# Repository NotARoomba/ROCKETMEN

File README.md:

<h1 align="center">
  <br>
  
  <br>
  ROCKETMEN
  <br>
</h1>

<h4 align="center">Project files for a custom model rocket and embedded flight controller.</h4>

<div align="center">

</div>

<p align="center">
  <a href="#key-features">Key Features</a> •
  <a href="#how-to-use">How To Use</a> •
  <a href="#credits">Credits</a> •
  <a href="#license">License</a>
</p>

## Key Features

- Small (12cm x 5cm) microcontroller with
  - STM32 MCU
  - USB-C with USB-Serial CH340 chip
  - LoRa communication at 433 Mhz from the LLCC68 chip
  - IMU that proides gyro/accelerometer data
  - Pressure and temperature sensors
- Website that provides data in real time (websockets)
- Client that sends data from the ground station to the website

## How To Use

To clone and run this application, you'll need [Git](https://git-scm.com) and [Rust](https://www.rust-lang.org/) installed on your computer. From your command line:

```bash
# Clone this repository
$ git clone https://github.com/NotARoomba/ROCKETMEN

# Go into the repository
$ cd ROCKETMEN

# Go into the server
$ cd Talos/Server

# Run the app
$ cargo run
```

## Credits

This software uses the following open source packages:

- [Rust](https://www.rust-lang.org/)
- [Node.js](https://nodejs.org/)

## You may also like...

- [Niveles De Niveles](https://github.com/NotARoomba/NivelesDeNiveles) - A real-time flood alert app
- [SupDoc](https://github.com/NotARoomba/SupDoc) - An app facilitating doctor/patient communication

## License

MIT

---

> [notaroomba.dev](https://notaroomba.dev) &nbsp;&middot;&nbsp;
> GitHub [@NotARoomba](https://github.com/NotARoomba) &nbsp;&middot;&nbsp;

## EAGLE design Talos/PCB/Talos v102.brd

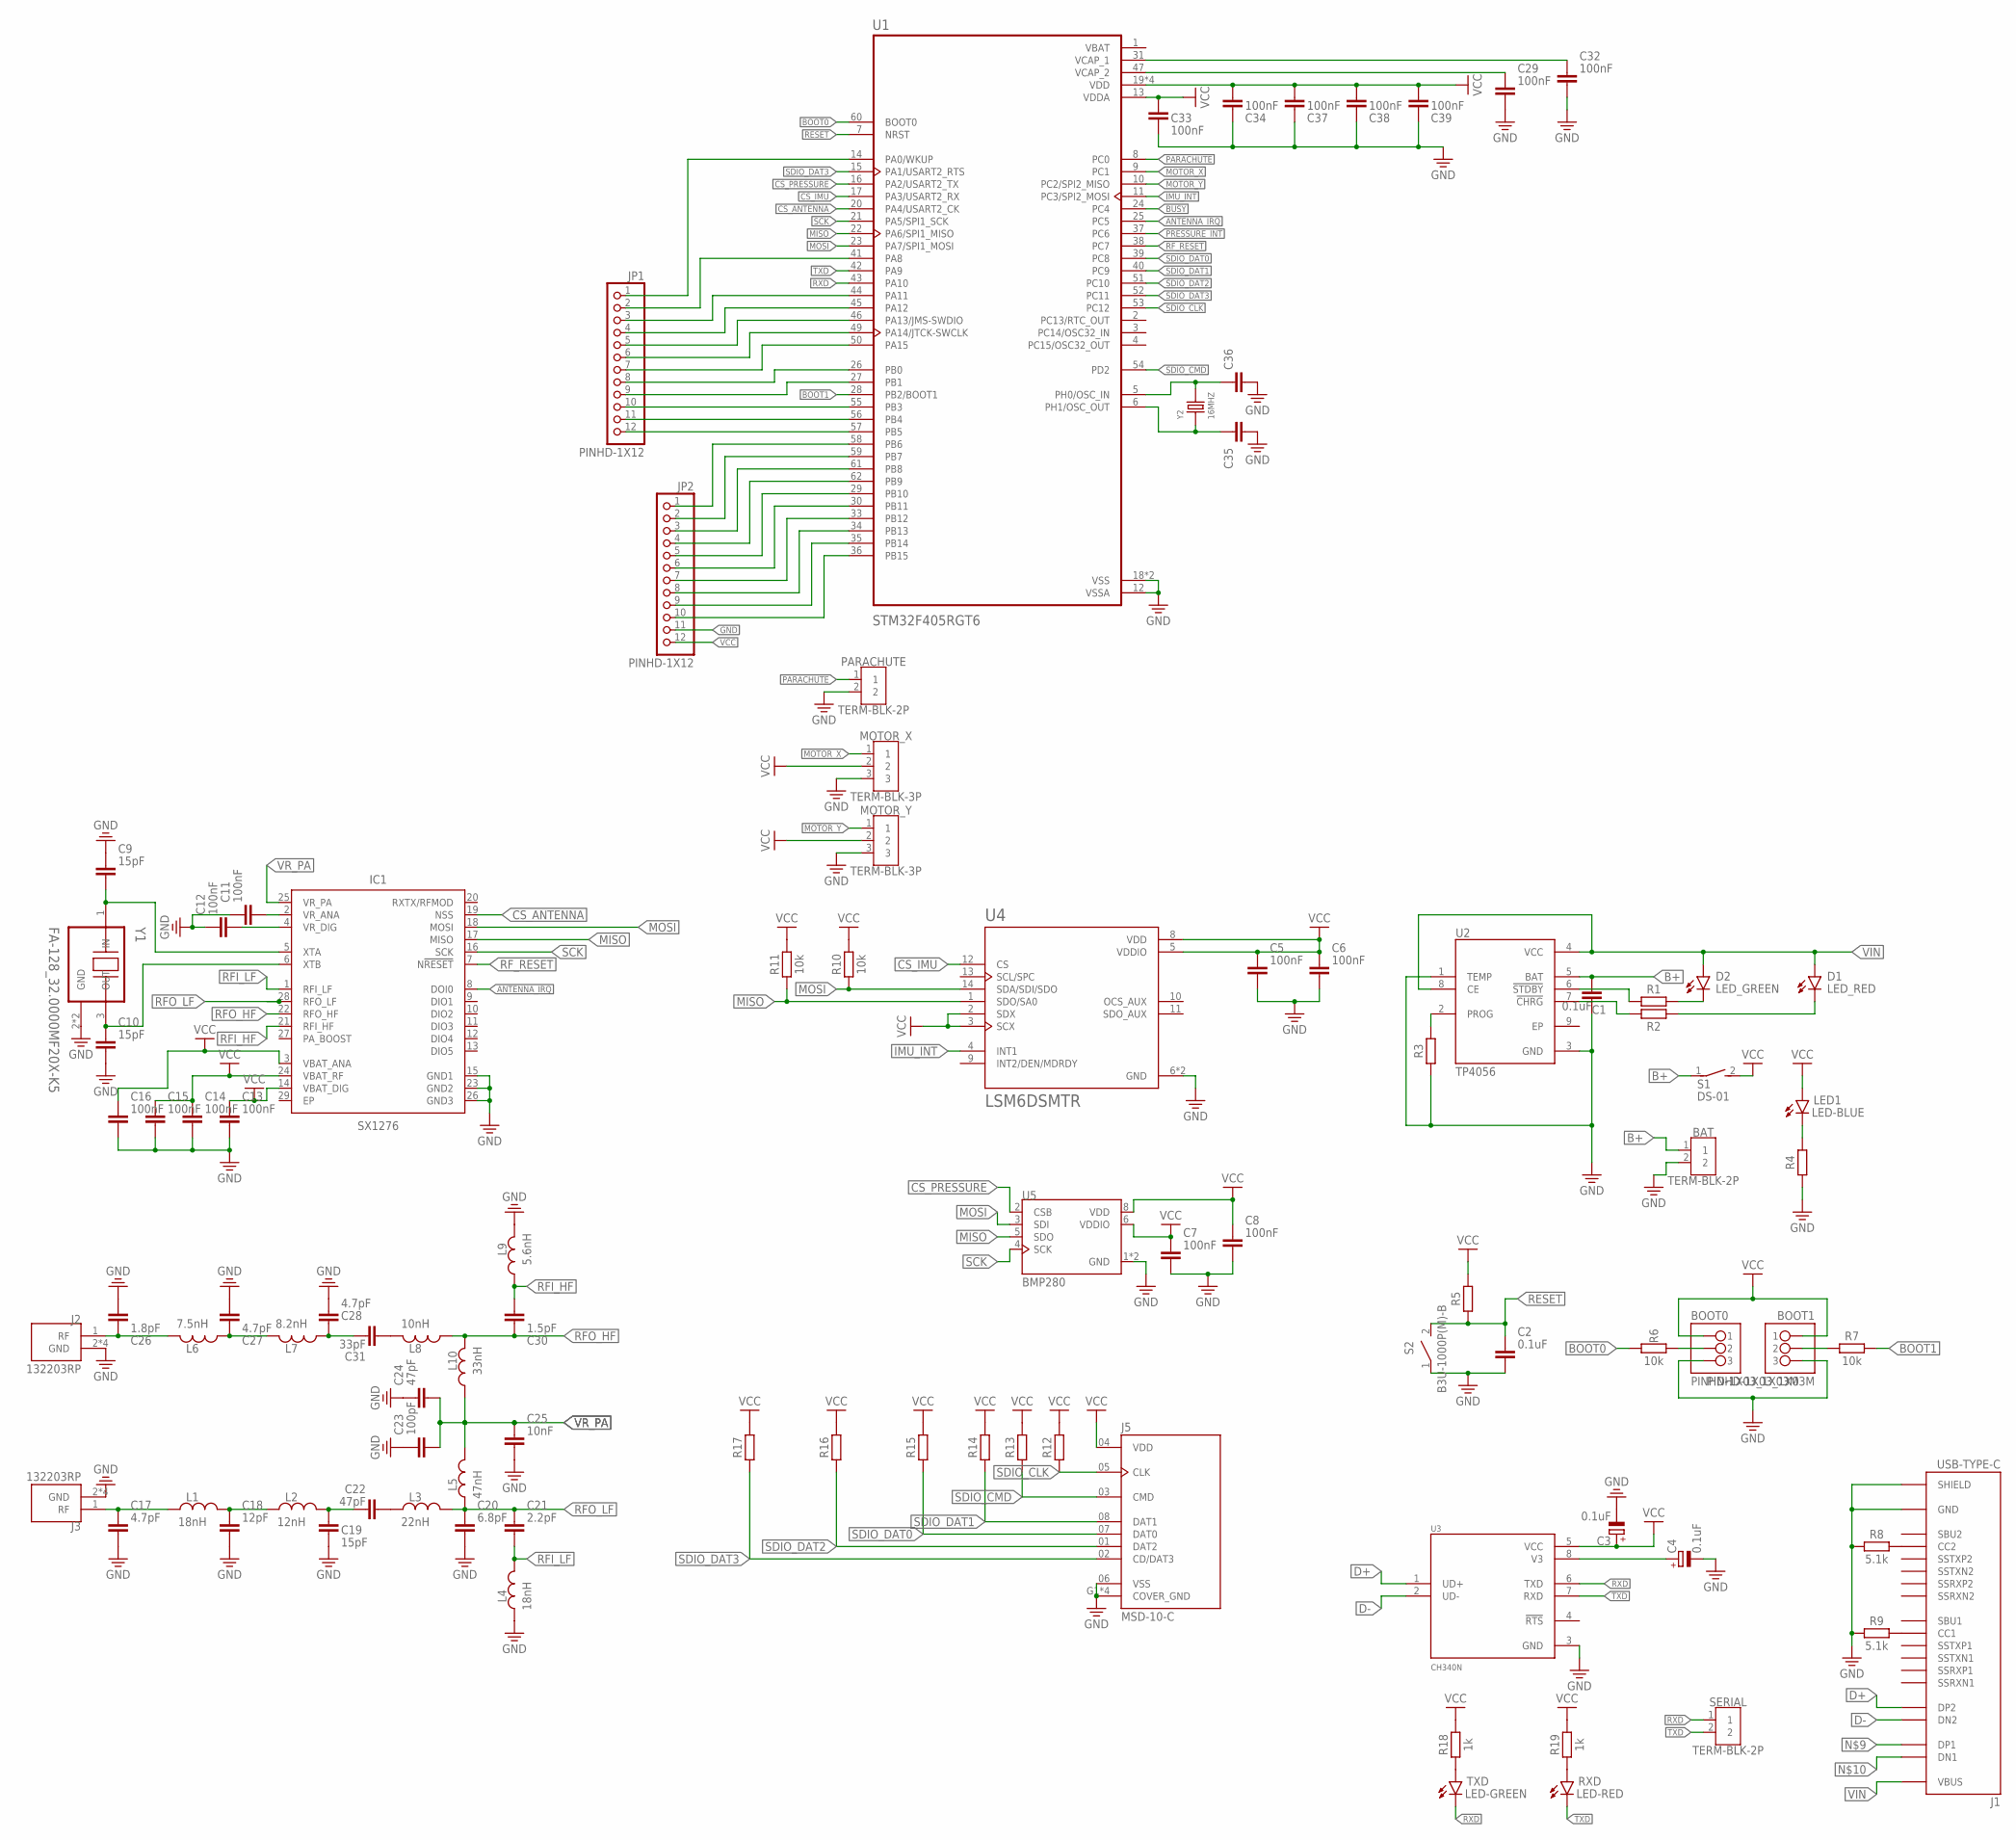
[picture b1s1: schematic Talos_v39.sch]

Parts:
BAT: TERM-BLK-2P; TERMBLK_254-2N
BOOT0, BOOT1: PINHD-1X03_1X03M; 1X03
C1, C2: 0.1uF; CAPC1005X60
C3, C4: 0.1uF; CAPMP3216X180N
C5, C6, C7, C8, C11, C12, C13, C14, C15, C16, C29, C32, C33, C34, C37, C38, C39: 100nF; CAPC1005X60
C9, C10, C19: 15pF; CAPC1005X60
C17, C27, C28: 4.7pF; CAPC1005X60
C18: 12pF; CAPC1005X60
C20: 6.8pF; CAPC1005X60
C21: 2.2pF; CAPC1005X60
C22, C24: 47pF; CAPC1005X60
C23: 100pF; CAPC1005X60
C25: 10nF; CAPC1005X60
C26: 1.8pF; CAPC1005X60
C30: 1.5pF; CAPC1005X60
C31: 33pF; CAPC1005X60
C35, C36: C_CHIP-0402(1005-METRIC); CAPC1005X60
D1: LED_RED; LEDC1608X35N_FLAT-R
D2: LED_GREEN; LEDC1608X35N_FLAT-G
IC1: SX1276; QFN65P600X600X100-29T480
J1: USB-TYPE-C; CUI_UJ31-CH-31-SMT-TR
J2, J3: 132203RP
J5: MSD-10-C; CUI_MSD-10-C
JP1, JP2: PINHD-1X12; 1X12
L1, L4: 18nH; INDC1006X60N
L2: 12nH; INDC1006X60N
L3: 22nH; INDC1006X60N
L5: 47nH; INDC1006X60N
L6: 7.5nH; INDC1006X60N
L7: 8.2nH; INDC1006X60N
L8: 10nH; INDC1006X60N
L9: 5.6nH; INDC1006X60N
L10: 33nH; INDC1006X60N
LED1: LED-BLUE; LEDC1608X39N_B
MOTOR_X: TERM-BLK-3P; TERMBLK_254-3N
MOTOR_Y: TERM-BLK-3P; TERMBLK_254-3N
PARACHUTE: TERM-BLK-2P; TERMBLK_254-2N
R1, R2, R4, R5, R12, R13, R14, R15, R16, R17: R_CHIP-0402(1005-METRIC); RESC1005X40
R3: RESISTOR__CHIP-0402(1005-METRIC); RESC1005X40
R6, R7, R10, R11: 10k; RESC1005X40
R8, R9: 5.1k; RESC1005X40
R18, R19: 1k; RESC1005X40
RXD: LED-RED; LEDC1608X39N_R
S1: DS-01
S2: B3U-1000P(M)-B
SERIAL: TERM-BLK-2P; TERMBLK_254-2N
TXD: LED-GREEN; LEDC1608X39N_G
U1: STM32F405RGT6; QFP50P1200X1200X160-64N
U2: TP4056; SOP127P600X175-9N
U3: CH340N; SOIC127P600X160-8N
U4: LSM6DSMTR; PQFN50P300X250X86-14N
U5: BMP280; XDCR_BMP280
Y1: FA-128_32.0000MF20X-K5; OSCCC200X160X50
Y2: 16MHZ; HC49US

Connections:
ANTENNA_IRQ: IC1.8 (DOI0), U1.25 (PC5)
B+: BAT.1, C1.2, S1.1, U2.5 (BAT)
BOOT0: R6.1, U1.60 (BOOT0)
BOOT1: R7.2, U1.28 (PB2/BOOT1)
BUSY: U1.24 (PC4)
CS_ANTENNA: IC1.19 (NSS), U1.20 (PA4/USART2_CK)
CS_IMU: U1.17 (PA3/USART2_RX), U4.12 (CS)
CS_PRESSURE: U1.16 (PA2/USART2_TX), U5.2 (CSB)
D+: J1.B6 (DP2), U3.1 (UD+)
D-: J1.B7 (DN2), U3.2 (UD-)
GND: BAT.2, BOOT0.3, BOOT1.3, C1.1, C2.2, C3.2 (-), C4.2 (-), C5.2, C6.2, C7.2, C8.2, C9.1, C10.2, C11.1, C12.1, C13.2, C14.2, C15.2, C16.2, C17.2, C18.2, C19.2, C20.2, C23.1, C24.1, C25.2, C26.2, C27.2, C28.2, C29.2, C32.2, C33.2, C34.2, C35.2, C36.2, C37.2, C38.2, C39.2, IC1.15 (GND1), IC1.23 (GND2), IC1.26 (GND3), J1.1 (SHIELD), J1.2 (SHIELD), J1.3 (SHIELD), J1.4 (SHIELD), J1.5 (SHIELD), J1.6 (SHIELD), J1.A1 (GND), J1.A12 (GND), J1.B1 (GND), J1.B12 (GND), J1.S1 (SHIELD), J1.S2 (SHIELD), J2.2 (GND), J2.3 (GND), J2.4 (GND), J2.5 (GND), J3.2 (GND), J3.3 (GND), J3.4 (GND), J3.5 (GND), J5.06 (VSS), J5.G1 (COVER_GND), J5.G2 (COVER_GND), J5.G3 (COVER_GND), J5.G4 (COVER_GND), JP2.11, L4.1, L9.1, MOTOR_X.3, MOTOR_Y.3, PARACHUTE.2, R3.1, R4.1, R8.1, R9.1, S2.1, U1.12 (VSSA), U1.18 (VSS), U1.63 (VSS), U2.1 (TEMP), U2.3 (GND), U3.3 (GND), U4.6 (GND), U4.7 (GND), U5.1 (GND), U5.7 (GND), Y1.2 (GND), Y1.4 (GND)
IMU_INT: U1.11 (PC3/SPI2_MOSI), U4.4 (INT1)
MISO: IC1.17 (MISO), R11.1, U1.22 (PA6/SPI1_MISO), U4.1 (SDO/SA0), U5.5 (SDO)
MOSI: IC1.18 (MOSI), R10.1, U1.23 (PA7/SPI1_MOSI), U4.14 (SDA/SDI/SDO), U5.3 (SDI)
MOTOR_X: MOTOR_X.1, U1.9 (PC1)
MOTOR_Y: MOTOR_Y.1, U1.10 (PC2/SPI2_MISO)
unnamed: D2.C, R1.2
unnamed: D1.C, R2.2
unnamed: R1.1, U2.6 (!STDBY)
unnamed: R2.1, U2.7 (!CHRG)
unnamed: R3.2, U2.2 (PROG)
unnamed: LED1.1 (C), R4.2
unnamed: BOOT0.2, R6.2
unnamed: BOOT1.2, R7.1
unnamed: J1.B5 (CC2), R8.2
unnamed: C4.1 (+), U3.8 (V3)
unnamed: J1.A5 (CC1), R9.2
unnamed: JP1.1, U1.14 (PA0/WKUP)
unnamed: JP1.2, U1.41 (PA8)
unnamed: C9.2, IC1.5 (XTA), Y1.1 (IN)
unnamed: C10.1, IC1.6 (XTB), Y1.3 (OUT)
unnamed: C11.2, IC1.2 (VR_ANA)
unnamed: C12.2, IC1.4 (VR_DIG)
unnamed: C17.1, J3.1 (RF), L1.1
unnamed: C18.1, L1.2, L2.1
unnamed: C19.1, C22.1, L2.2
unnamed: C26.1, J2.1 (RF), L6.1
unnamed: C27.1, L6.2, L7.1
unnamed: C22.2, L3.1
unnamed: C28.1, C31.1, L7.2
unnamed: C31.2, L8.1
unnamed: C32.1, U1.31 (VCAP_1)
unnamed: C29.1, U1.47 (VCAP_2)
unnamed: JP1.3, U1.44 (PA11)
unnamed: JP1.4, U1.45 (PA12)
unnamed: JP1.5, U1.46 (PA13/JMS-SWDIO)
unnamed: JP1.6, U1.49 (PA14/JTCK-SWCLK)
unnamed: JP1.7, U1.50 (PA15)
unnamed: JP1.8, U1.26 (PB0)
unnamed: JP1.9, U1.27 (PB1)
unnamed: JP1.10, U1.55 (PB3)
unnamed: JP1.11, U1.56 (PB4)
unnamed: JP1.12, U1.57 (PB5)
unnamed: JP2.1, U1.58 (PB6)
unnamed: JP2.2, U1.59 (PB7)
unnamed: JP2.3, U1.61 (PB8)
unnamed: JP2.4, U1.62 (PB9)
unnamed: JP2.5, U1.29 (PB10)
unnamed: JP2.6, U1.30 (PB11)
unnamed: JP2.7, U1.33 (PB12)
unnamed: JP2.8, U1.34 (PB13)
unnamed: JP2.9, U1.35 (PB14)
unnamed: JP2.10, U1.36 (PB15)
unnamed: R19.1, RXD.2 (A)
unnamed: R18.1, TXD.2 (A)
OSC_IN: C36.1, U1.5 (PH0/OSC_IN), Y2.2
OSC_OUT: C35.1, U1.6 (PH1/OSC_OUT), Y2.1
PARACHUTE: PARACHUTE.1, U1.8 (PC0)
PRESSURE_INT: U1.37 (PC6)
RESET: C2.1, R5.1, S2.2, U1.7 (NRST)
RFI_HF: C30.2, IC1.21 (RFI_HF), L9.2
RFI_LF: C21.2, IC1.1 (RFI_LF), L4.2
RFO_HF: C30.1, IC1.22 (RFO_HF), L8.2, L10.1
RFO_LF: C20.1, C21.1, IC1.28 (RFO_LF), L3.2, L5.1
RF_RESET: IC1.7 (N!RESET!), U1.38 (PC7)
RXD: SERIAL.1, TXD.1 (C), U1.43 (PA10), U3.6 (TXD)
SCK: IC1.16 (SCK), U1.21 (PA5/SPI1_SCK), U5.4 (SCK)
SDIO_CLK: J5.05 (CLK), R12.1, U1.53 (PC12)
SDIO_CMD: J5.03 (CMD), R13.1, U1.54 (PD2)
SDIO_DAT0: J5.07 (DAT0), R15.1, U1.39 (PC8)
SDIO_DAT1: J5.08 (DAT1), R14.1, U1.40 (PC9)
SDIO_DAT2: J5.01 (DAT2), R16.1, U1.51 (PC10)
SDIO_DAT3: J5.02 (CD/DAT3), R17.1, U1.15 (PA1/USART2_RTS), U1.52 (PC11)
TXD: RXD.1 (C), SERIAL.2, U1.42 (PA9), U3.7 (RXD)
VBAT: U1.1 (VBAT)
VCC: BOOT0.1, BOOT1.1, C3.1 (+), C5.1, C6.1, C7.1, C8.1, C13.1, C14.1, C15.1, C16.1, C33.1, C34.1, C37.1, C38.1, C39.1, IC1.3 (VBAT_ANA), IC1.14 (VBAT_DIG), IC1.24 (VBAT_RF), J5.04 (VDD), JP2.12, LED1.2 (A), MOTOR_X.2, MOTOR_Y.2, R5.2, R10.2, R11.2, R12.2, R13.2, R14.2, R15.2, R16.2, R17.2, R18.2, R19.2, S1.2, U1.13 (VDDA), U1.19 (VDD), U1.32 (VDD), U1.48 (VDD), U1.64 (VDD), U3.5 (VCC), U4.2 (SDX), U4.3 (SCX), U4.5 (VDDIO), U4.8 (VDD), U5.6 (VDDIO), U5.8 (VDD)
VIN: D1.A, D2.A, J1.A4 (VBUS), J1.A9 (VBUS), J1.B4 (VBUS), J1.B9 (VBUS), U2.4 (VCC), U2.8 (CE)
VR_PA: C23.2, C24.2, C25.1, IC1.25 (VR_PA), L5.2, L10.2

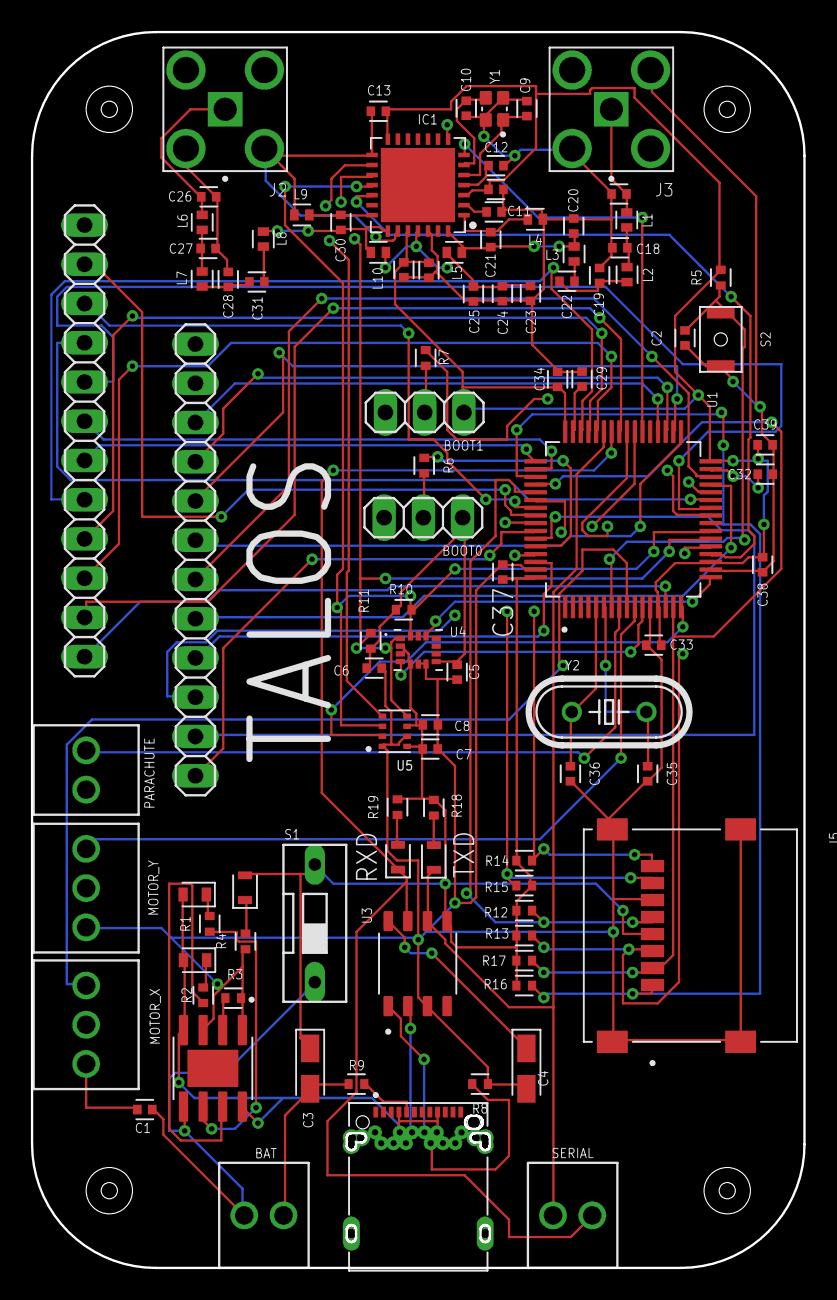
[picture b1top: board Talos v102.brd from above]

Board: 4 copper layers, 50.0 x 80.0 mm, 96 parts (0 on the bottom side), 85 nets.

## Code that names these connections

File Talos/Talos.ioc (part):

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Mcu.Name=STM32F405RGTx
Mcu.Package=LQFP64
Mcu.UserName=STM32F405RGTx
PA1.GPIOParameters=GPIO_Label
PA1.GPIO_Label=SD_CD
PA1.Signal=GPIO_Input
PA10.GPIOParameters=GPIO_Label
PA10.GPIO_Label=RXD
PA10.Mode=Asynchronous
PA10.Signal=USART1_RX
PA15.Mode=NSS_Signal_Hard_Output
PA15.Signal=SPI1_NSS
PA2.GPIOParameters=GPIO_Label
PA2.GPIO_Label=CS_PRESSURE
PA2.Signal=GPIO_Output
PA3.GPIOParameters=GPIO_Label
PA3.GPIO_Label=CS_GYRO
PA3.Signal=GPIO_Output
PA4.GPIOParameters=GPIO_Label
PA4.GPIO_Label=CS_WIRELESS
PA4.Signal=GPIO_Output
PA5.GPIOParameters=GPIO_Label
PA5.GPIO_Label=SCK
PA5.Mode=Full_Duplex_Master
PA5.Signal=SPI1_SCK
PA6.GPIOParameters=GPIO_Label
PA6.GPIO_Label=MISO
PA6.Mode=Full_Duplex_Master
PA6.Signal=SPI1_MISO
PA7.GPIOParameters=GPIO_Label
PA7.GPIO_Label=MOSI
PA7.Mode=Full_Duplex_Master
PA7.Signal=SPI1_MOSI
PA9.GPIOParameters=GPIO_Label
PA9.GPIO_Label=TXD
PA9.Mode=Asynchronous
PA9.Signal=USART1_TX
PB6.GPIOParameters=GPIO_Label
PB6.GPIO_Label=SCL
PB6.Mode=I2C
PB6.Signal=I2C1_SCL
PB7.GPIOParameters=GPIO_Label
PB7.GPIO_Label=SDA
PB7.Mode=I2C
PB7.Signal=I2C1_SDA
PC0.GPIOParameters=GPIO_Label
PC0.GPIO_Label=PARACHUTE
PC0.Signal=GPIO_Output
PC1.GPIOParameters=GPIO_Label
PC1.GPIO_Label=MOTOR_X
PC1.Signal=GPIO_Output
PC12.Mode=SD_1_bit
PC12.Signal=SDIO_CK
PC2.GPIOParameters=GPIO_Label
PC2.GPIO_Label=MOTOR_Y
PC2.Signal=GPIO_Output
PC3.GPIOParameters=GPIO_Label
PC3.GPIO_Label=IMU_INT
PC3.Signal=EVENTOUT
PC4.Signal=GPIO_Input
PC5.GPIOParameters=GPIO_Label
PC5.GPIO_Label=ANTENNA_IRQ
PC5.Signal=GPIO_Input
PC6.GPIOParameters=GPIO_Label
PC6.GPIO_Label=PRESSURE_INT
PC6.Signal=EVENTOUT
PC7.GPIOParameters=GPIO_Label
PC7.GPIO_Label=RF_RESET
PC7.Signal=GPIO_Output
PC8.Mode=SD_1_bit
PC8.Signal=SDIO_D0
PD2.Mode=SD_1_bit
PD2.Signal=SDIO_CMD
PH0-OSC_IN.Signal=RCC_OSC_IN
PH1-OSC_OUT.Signal=RCC_OSC_OUT
RCC.HSE_VALUE=25000000
RCC.SYSCLKFreq_VALUE=16000000
board=custom

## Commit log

2024-12-12 stuff
2024-12-13 temp
2024-12-14 added imu demonstration
2024-12-19 add website
2024-12-19 rust client
2024-12-20 add lora code
2024-12-20 add website and server cod
2024-12-20 addeds tuff
2024-12-22 added test mode
2024-12-22 add a visualization
2024-12-25 prettier
2024-12-27 Create CNAME
2024-12-27 added tls and docs
2024-12-27 added openssl
2024-12-27 port
2024-12-27 add hyper
2024-12-27 error handling
2024-12-27 fix assets dir
2024-12-27 add tracing and build
2024-12-27 add wss
2024-12-27 whoops preload
2024-12-27 graph
2024-12-28 bmp580
2024-12-29 research paper start
2024-12-29 updated paper
2024-12-29 revisions
2024-12-29 draft 1
2024-12-29 website
2024-12-29 small edits
2024-12-29 words
2024-12-29 updated with grammarly
2025-01-08 more stuff
2025-01-09 readme
2025-06-02 added stuff
2025-06-03 added stuff and filter
